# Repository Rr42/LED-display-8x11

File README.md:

# 8 by 11 LED display
A basic 8x11 LED display that can be driven by an Arduino or a Raspberry Pi board.

The LED matrix and hardware driver are designed using KiCAD (5.1.6) and the layout is made with perfboards in mind, so the front layer can be used as wires and the back layer for solder traces.

### Rendered LED display

### Fabricated and assembled LED display

## Using the Arduino library
To include and use the display library in sketches made using the Arduino IDE, first the library folder follow the below steps:
* Copy the `LED8x11_display_lib` folder from `LED-display/Software`
    * To `My Documents\Arduino\libraries` in Windows.
    * To `~/Documents/Arduino/libraries/` in linux. 
> For more details refer to the [libraries page](https://www.arduino.cc/en/hacking/libraries) on the Arduino website.
* Include the library header in the sketch
```cpp
#include <LED8x11_display_lib.h>
```

## Using the Raspberry Pi libraries
### Python
To use the Python display library follow the below steps:
> This Python display library requires the `RPi.GPIO` Python library. To setup `RPi.GPIO` refer to [PyPI/RPi.GPIO](https://pypi.org/project/RPi.GPIO/).
* Move to the `Software/RaspberryPi/Python/LED8x11_display_lib` directory
```
cd Software/RaspberryPi/Python/LED8x11_display_lib
```
* Run the Python setup script
> Admin/root privilages may be required to install the library
```
python3 setup.py install
```
* Import the library in your program
```python
from led8x11displaylib import display8x11
```
### C++
To use the C++ display library follow the below steps:
> This C++ display library requires the `wiringPi` library. To setup `wiringPi` refer to the official [Wiring Pi](http://wiringpi.com/download-and-install/) site.
* Move to the `Software/RaspberryPi/Cpp/LED8x11_display_lib` directory
```
cd Software/RaspberryPi/Cpp/LED8x11_display_lib
```
* Run the make command (this will build the library and all the examples)
```
make all
```
* Include the library header in your program using the following line
```cpp
#include "LED8x11_display_lib.hpp"
```
* While compilint the program link to both `wiringPi` and `led8x11display`
```
g++ myprogram.cpp -o myprogram -L<path/to/Cpp/folder>/build/lib -L/usr/lib -lled8x11display -lwiringPi ...
```

To reset/clean the C++ objectfile run the following in `Software/RaspberryPi/Cpp`:
```
make clean
```

## License
The Software and firmware of this project is licensed under the the MIT license however the hardware is under the [Open Source Hardware](https://www.oshwa.org/definition/) license.

## To do
* Firmware driver and APIs for Raspberry Pi.
    * Example code (Python and C++)
* Documentation for hardware

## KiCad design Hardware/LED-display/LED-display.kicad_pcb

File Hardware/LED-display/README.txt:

# Read me for LED Display 8x11 hardware

This project is created using KiCAD (v5.1.6).

This is a simple 8x11 LED matrix driver that can interface with an Arduino or a Raspberry Pi board.

The layout has been created with perfboards in mind (with the front layer being wires and the back layer being sloder traces) and therefore is not the most optimal for manufacturing.

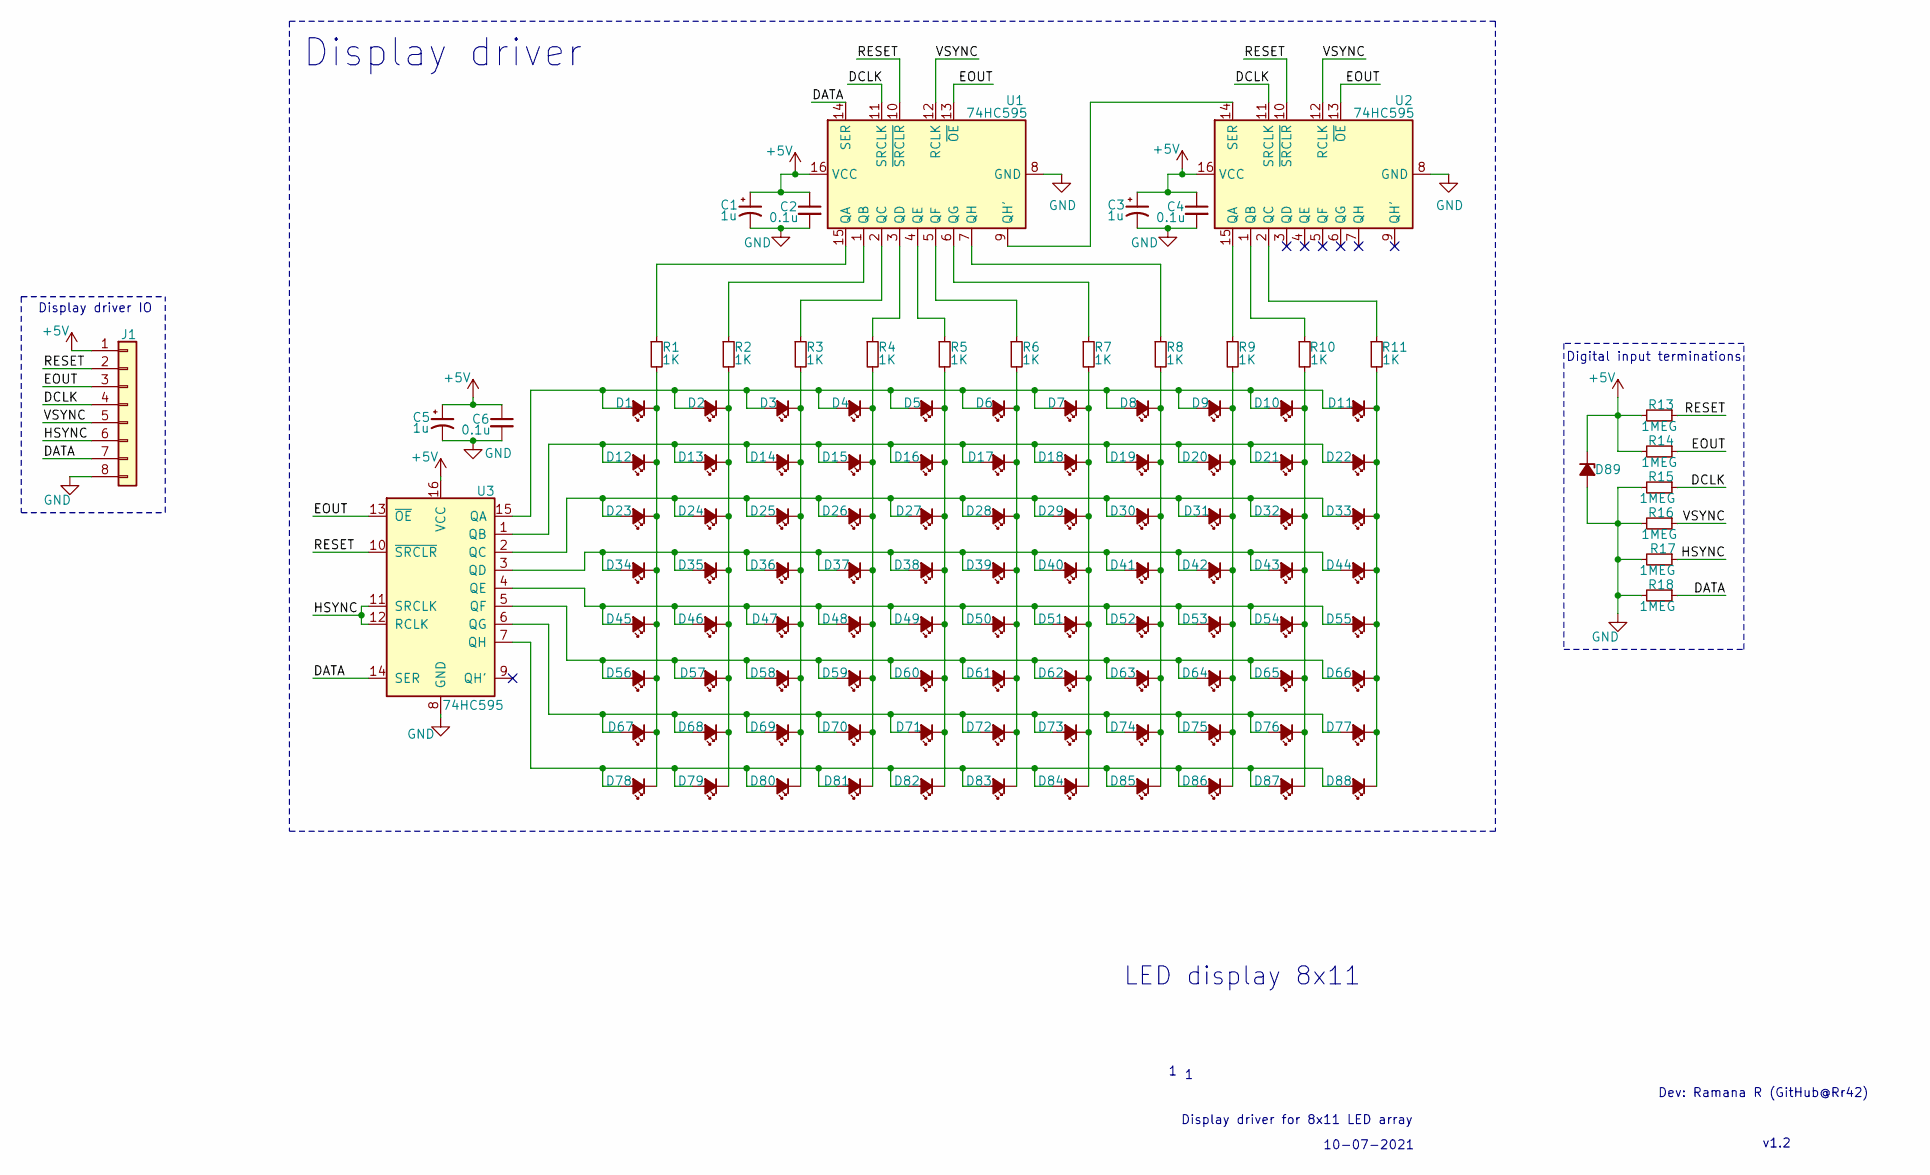
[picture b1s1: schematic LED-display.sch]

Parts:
C1, C3, C5: 1u; CP_Radial_D5.0mm_P2.00mm
C2, C4, C6: 0.1u; C_Disc_D5.1mm_W3.2mm_P5.00mm
D1, D2, D3, D4, D5, D6, D7, D8, D9, D10, D11, D12, D13, D14, D15, D16, D17, D18, D19, D20, D21, D22, D23, D24, D25, D26, D27, D28, D29, D30, D31, D32, D33, D34, D35, D36, D37, D38, D39, D40, D41, D42, D43, D44, D45, D46, D47, D48, D49, D50, D51, D52, D53, D54, D55, D56, D57, D58, D59, D60, D61, D62, D63, D64, D65, D66, D67, D68, D69, D70, D71, D72, D73, D74, D75, D76, D77, D78, D79, D80, D81, D82, D83, D84, D85, D86, D87, D88: LED_White; LED_D5.0mm
D89: D_Zener_Small_ALT; D_DO-35_SOD27_P7.62mm_Horizontal
J1: Conn_01x08; PinHeader_1x08_P2.54mm_Vertical
R1, R2, R3, R4, R5, R6, R7, R8, R9, R10, R11: 1K; R_Axial_DIN0207_L6.3mm_D2.5mm_P10.16mm_Horizontal
R13, R14, R15, R16, R17, R18: 1MEG; R_Axial_DIN0207_L6.3mm_D2.5mm_P10.16mm_Horizontal
U1, U2, U3: 74HC595; DIP-16_W7.62mm

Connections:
+5V: C1.1, C2.1, C3.1, C4.1, C5.1, C6.1, D89.1 (K), J1.1, R13.2, R14.2, U1.16 (VCC), U2.16 (VCC), U3.16 (VCC)
/DATA: J1.7, R18.1, U1.14 (SER), U3.14 (SER)
/DCLK: J1.4, R15.1, U1.11 (SRCLK), U2.11 (SRCLK)
/EOUT: J1.3, R14.1, U1.13 (~OE), U2.13 (~OE), U3.13 (~OE)
/HSYNC: J1.6, R17.1, U3.11 (SRCLK), U3.12 (RCLK)
/RESET: J1.2, R13.1, U1.10 (~SRCLR), U2.10 (~SRCLR), U3.10 (~SRCLR)
/VSYNC: J1.5, R16.1, U1.12 (RCLK), U2.12 (RCLK)
GND: C1.2, C2.2, C3.2, C4.2, C5.2, C6.2, D89.2 (A), J1.8, R15.2, R16.2, R17.2, R18.2, U1.8 (GND), U2.8 (GND), U3.8 (GND)
unnamed: D1.1 (K), D12.1 (K), D23.1 (K), D34.1 (K), D45.1 (K), D56.1 (K), D67.1 (K), D78.1 (K), R1.2
unnamed: D1.2 (A), D2.2 (A), D3.2 (A), D4.2 (A), D5.2 (A), D6.2 (A), D7.2 (A), D8.2 (A), D9.2 (A), D10.2 (A), D11.2 (A), U3.15 (QA)
unnamed: D10.1 (K), D21.1 (K), D32.1 (K), D43.1 (K), D54.1 (K), D65.1 (K), D76.1 (K), D87.1 (K), R10.2
unnamed: D11.1 (K), D22.1 (K), D33.1 (K), D44.1 (K), D55.1 (K), D66.1 (K), D77.1 (K), D88.1 (K), R11.2
unnamed: D12.2 (A), D13.2 (A), D14.2 (A), D15.2 (A), D16.2 (A), D17.2 (A), D18.2 (A), D19.2 (A), D20.2 (A), D21.2 (A), D22.2 (A), U3.1 (QB)
unnamed: D2.1 (K), D13.1 (K), D24.1 (K), D35.1 (K), D46.1 (K), D57.1 (K), D68.1 (K), D79.1 (K), R2.2
unnamed: D3.1 (K), D14.1 (K), D25.1 (K), D36.1 (K), D47.1 (K), D58.1 (K), D69.1 (K), D80.1 (K), R3.2
unnamed: D4.1 (K), D15.1 (K), D26.1 (K), D37.1 (K), D48.1 (K), D59.1 (K), D70.1 (K), D81.1 (K), R4.2
unnamed: D5.1 (K), D16.1 (K), D27.1 (K), D38.1 (K), D49.1 (K), D60.1 (K), D71.1 (K), D82.1 (K), R5.2
unnamed: D6.1 (K), D17.1 (K), D28.1 (K), D39.1 (K), D50.1 (K), D61.1 (K), D72.1 (K), D83.1 (K), R6.2
unnamed: D7.1 (K), D18.1 (K), D29.1 (K), D40.1 (K), D51.1 (K), D62.1 (K), D73.1 (K), D84.1 (K), R7.2
unnamed: D8.1 (K), D19.1 (K), D30.1 (K), D41.1 (K), D52.1 (K), D63.1 (K), D74.1 (K), D85.1 (K), R8.2
unnamed: D9.1 (K), D20.1 (K), D31.1 (K), D42.1 (K), D53.1 (K), D64.1 (K), D75.1 (K), D86.1 (K), R9.2
unnamed: D23.2 (A), D24.2 (A), D25.2 (A), D26.2 (A), D27.2 (A), D28.2 (A), D29.2 (A), D30.2 (A), D31.2 (A), D32.2 (A), D33.2 (A), U3.2 (QC)
unnamed: D34.2 (A), D35.2 (A), D36.2 (A), D37.2 (A), D38.2 (A), D39.2 (A), D40.2 (A), D41.2 (A), D42.2 (A), D43.2 (A), D44.2 (A), U3.3 (QD)
unnamed: D45.2 (A), D46.2 (A), D47.2 (A), D48.2 (A), D49.2 (A), D50.2 (A), D51.2 (A), D52.2 (A), D53.2 (A), D54.2 (A), D55.2 (A), U3.4 (QE)
unnamed: D56.2 (A), D57.2 (A), D58.2 (A), D59.2 (A), D60.2 (A), D61.2 (A), D62.2 (A), D63.2 (A), D64.2 (A), D65.2 (A), D66.2 (A), U3.5 (QF)
unnamed: D67.2 (A), D68.2 (A), D69.2 (A), D70.2 (A), D71.2 (A), D72.2 (A), D73.2 (A), D74.2 (A), D75.2 (A), D76.2 (A), D77.2 (A), U3.6 (QG)
unnamed: D78.2 (A), D79.2 (A), D80.2 (A), D81.2 (A), D82.2 (A), D83.2 (A), D84.2 (A), D85.2 (A), D86.2 (A), D87.2 (A), D88.2 (A), U3.7 (QH)
unnamed: R1.1, U1.15 (QA)
unnamed: R2.1, U1.1 (QB)
unnamed: R3.1, U1.2 (QC)
unnamed: R4.1, U1.3 (QD)
unnamed: R5.1, U1.4 (QE)
unnamed: R6.1, U1.5 (QF)
unnamed: R7.1, U1.6 (QG)
unnamed: R8.1, U1.7 (QH)
unnamed: R9.1, U2.15 (QA)
unnamed: R10.1, U2.1 (QB)
unnamed: R11.1, U2.2 (QC)
unnamed: U1.9 (QH'), U2.14 (SER)

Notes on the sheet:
10-07-2021
v1.2
Display driver
Display driver IO
Display driver for 8x11 LED array
Dev: Ramana R (GitHub@Rr42)
LED display 8x11
Digital input terminations

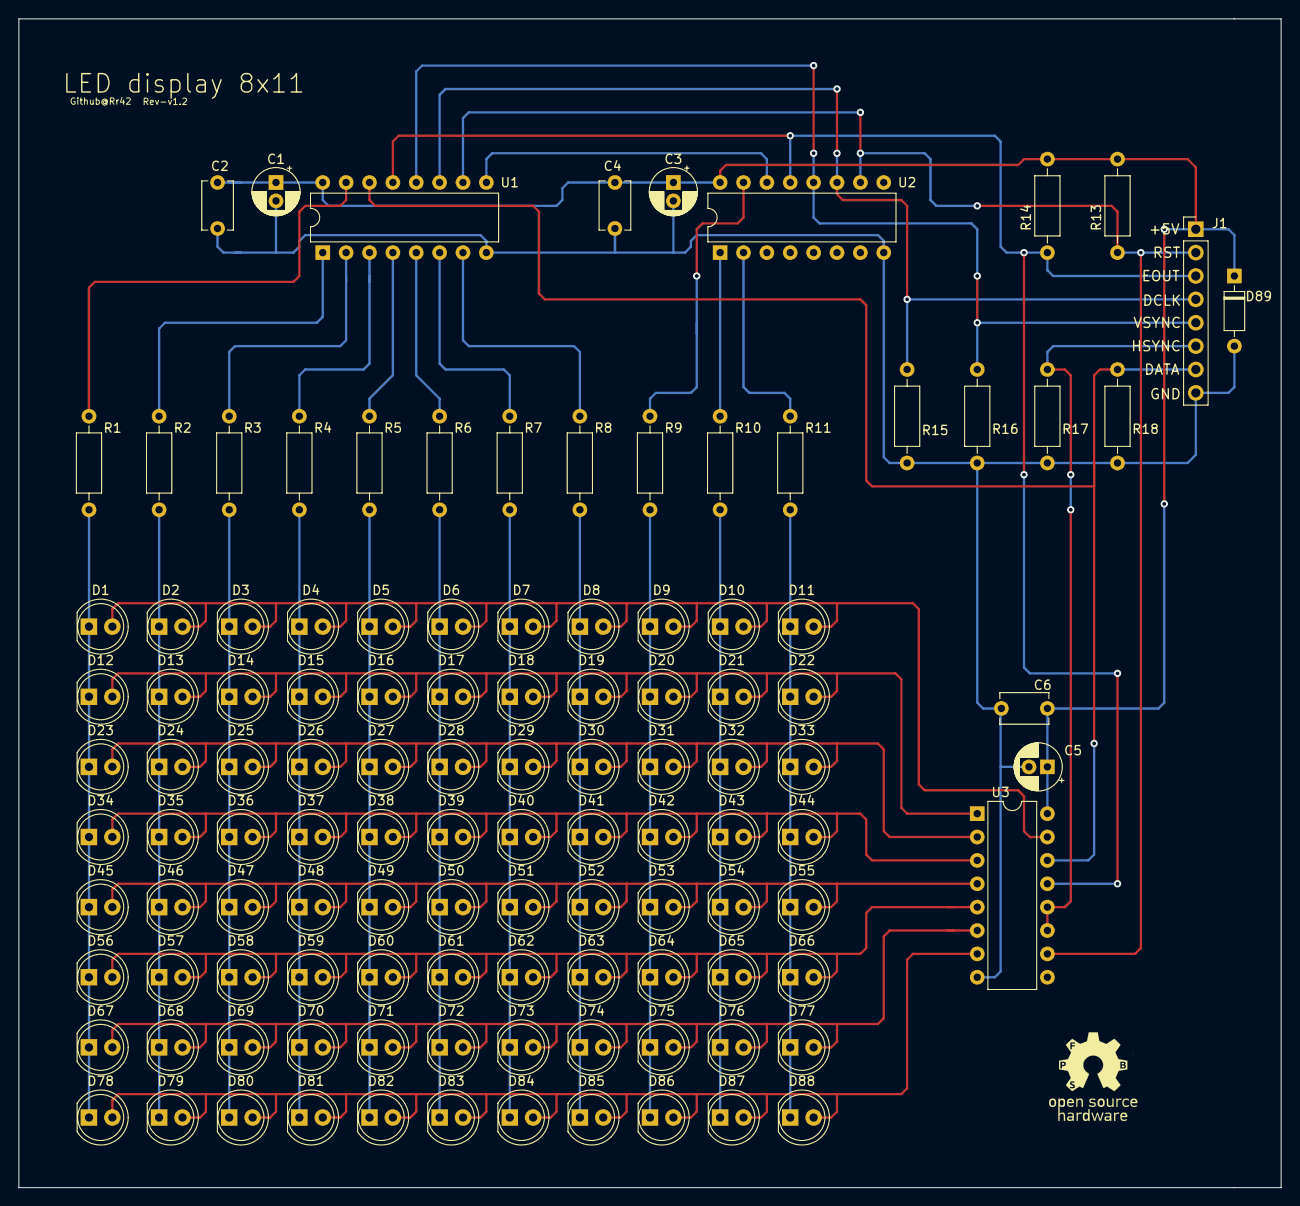
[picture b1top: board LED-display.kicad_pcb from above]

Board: 2 copper layers, 137.2 x 127.0 mm, 116 parts (0 on the bottom side), 39 nets.

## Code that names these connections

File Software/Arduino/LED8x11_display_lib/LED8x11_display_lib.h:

/******************************************************************
* File name: LED8x11_display_lib.h
* Version: v1.0
* DEV: GitHub@Rr42
* Description:
*  Display library header for the 8x11 LED display.
******************************************************************/
#ifndef __LED8X11_DISPLAY_LIB__

#define __LED8X11_DISPLAY_LIB__
#include <Arduino.h>

/* Display size */
#define LINE_LENGTH 11
#define LINE_COUNT 8

/* Referesh rate calibration data */
/* Minimum parasitic time between each line in microseconds */
#define PARASITIC_LINE_TIME 192
/* Minimum parasitic time between each frame in milliseconds (including intermediate resets) */
#define PARASITIC_FRAME_TIME 1.6
/* Targeted default display refresh rate in Hz */
#define DEFAULT_REFRESH_RATE 60

/* Connector length */
#define CON_LEN 6

/* Display driver class */
class LedDisplay {
private:
    /* Display brightness (0 to 1) */
    float brightness;
    /* Calculated line time used to match delay */
    uint16_t line_time_delay;
    /* Display refresh rate in Hz */
    float refresh_rate;
    /* Storage for next line index */
    uint8_t next_line; // Initialised in setup()
    /* Connector pin map */
    const uint8_t RESET, EOUT, DCLK, VSYNC, HSYNC, DATA;

protected:
    /* Protected function headers */
    void nextLine();

public:
    /* Class constructor */
    LedDisplay(uint8_t RESET, uint8_t EOUT, uint8_t DCLK, uint8_t VSYNC, uint8_t HSYNC, uint8_t DATA);
    /* Class destructor */
    ~LedDisplay();

    /* Public function headers */
    void showFrame(const uint8_t frame[LINE_COUNT][LINE_LENGTH], float time);
    void showFrame(const uint16_t frame[LINE_COUNT], float time);
    void initialise(float brightness, float refresh_rate);
    void sendLine(const uint8_t line[LINE_LENGTH]);
    void setRefreshRate(float refresh_rate);
    void setBrightness(float brightness);
    void sendLine(const uint16_t line);
    uint16_t getLineDelay();
    void displayRefresh();
    void displayReset();
    void initialise();
};
#endif

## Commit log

2021-03-20 First commit > Added KiCAD project files > Added placeholder for Software files
2021-03-20 Added license information
2021-07-03 Updated layout and reduced number of vias
2021-07-10 Replaced parllel 2.2K resistors with 1k to match other LEDs
2021-08-15 Re-adding oshw logo in layout
2021-08-24 Adding example programs for Arduino > Adding basic driver for Arduino based control > Adding 1 example for switching patterns
2021-08-24 Adding image of fabricated and assembled display
2021-08-24 Adding images of example patterns
2021-08-24 Updating assembled display image
2021-08-25 Adding example for brightness control
2021-08-25 Adding support for bit array based frames to allow better storage efficiency
2021-08-25 Incrementing file version numbers
2021-08-25 Adding consolidated display library and example for Arduino
2021-08-26 Rearranging directory structure of Arduino library to match requirements of the Arduino IDE
2021-08-26 Adding bouncy ball example for Arduino
2021-08-26 Updating Arduino example 3 with randomized ball positioning
2021-08-26 Updating gitignore to exclude build folders
2021-08-27 Adding pong to Arduino examples
2021-08-29 Updating layout with additional headroom for pins > Updating DIP-16 footprint for easier placement > Updating resistor footprints to allow earier placement > Adding silk for connector pin names
2021-08-29 Updating README with layout updates
2021-09-07 Patching display flicker when using brightness control. > Adjusting PWM frequency in examples to reduce flicker..
2021-09-11 Adding placeholder Raspberry Pi libraries and examples
2021-09-12 Patching bug where PWM frequency bits where not set properly
2023-07-06 Adding firmware for Arduino Nano based pong game board
    * Adding additional examples for Arduino Nano
